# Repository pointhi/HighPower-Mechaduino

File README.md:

View this project on [CADLAB.io](https://cadlab.io/project/1867). 

# HighPower-Mechaduino

KiCad based Mechaduino derivative which drives up to 10A.

This is the original Meachaduino Project: https://hackaday.io/project/11224-mechaduino

**Warning: This Board is currently under development. Simply fabricating it doesn't mean it would work!**
See [v0.1_BUILD_LOG.md](https://github.com/pointhi/HighPower-Mechaduino/blob/master/v0.1_BUILD_LOG.md) for some problems
found while building the first prototype.

A big thanks to the [Shuttleworth Foundation](https://shuttleworthfoundation.org) for supporting the development of this Project.

### Improvements

* ESD protection (especially USB)
* flyback diodes
* stronger drivers
* better silkscreen
* correct use of blocking capacitors
* fuse (for protection against polarity reversal and shorts)
* input voltage measurement
* supply of the microcontroller via the motor voltage supply
* external storage for calibration and configuration data
* Temperature sensor

### Planned Electrical/Mechanical Ratings

* Input Voltage-range of about 12V-50V
* N-Mosfet Driver which is capable of about 10A
* board in the size of NEMA 23 (56x56xmm) or NEMA 24 (60x60mm)

### Interfaces

* USB
* UART (3.3V)
* Step/Dir/Enable (PoStep25-32 Compatible)

### various informations

* [BOM](https://rawgit.com/pointhi/HighPower-Mechaduino/master/pcb/HighPower-Mechaduino.html) can be created using [KiBoM](https://github.com/SchrodingersGat/KiBoM)
* There exists a modified version of the Firmware for this project: [ElektronikNode/Mechaduino-Firmware](https://github.com/ElektronikNode/Mechaduino-Firmware)

## License

Hardware including documentation is licensed under [CERN OHL v.1.2. license](http://www.ohwr.org/licenses/cern-ohl/v1.2)

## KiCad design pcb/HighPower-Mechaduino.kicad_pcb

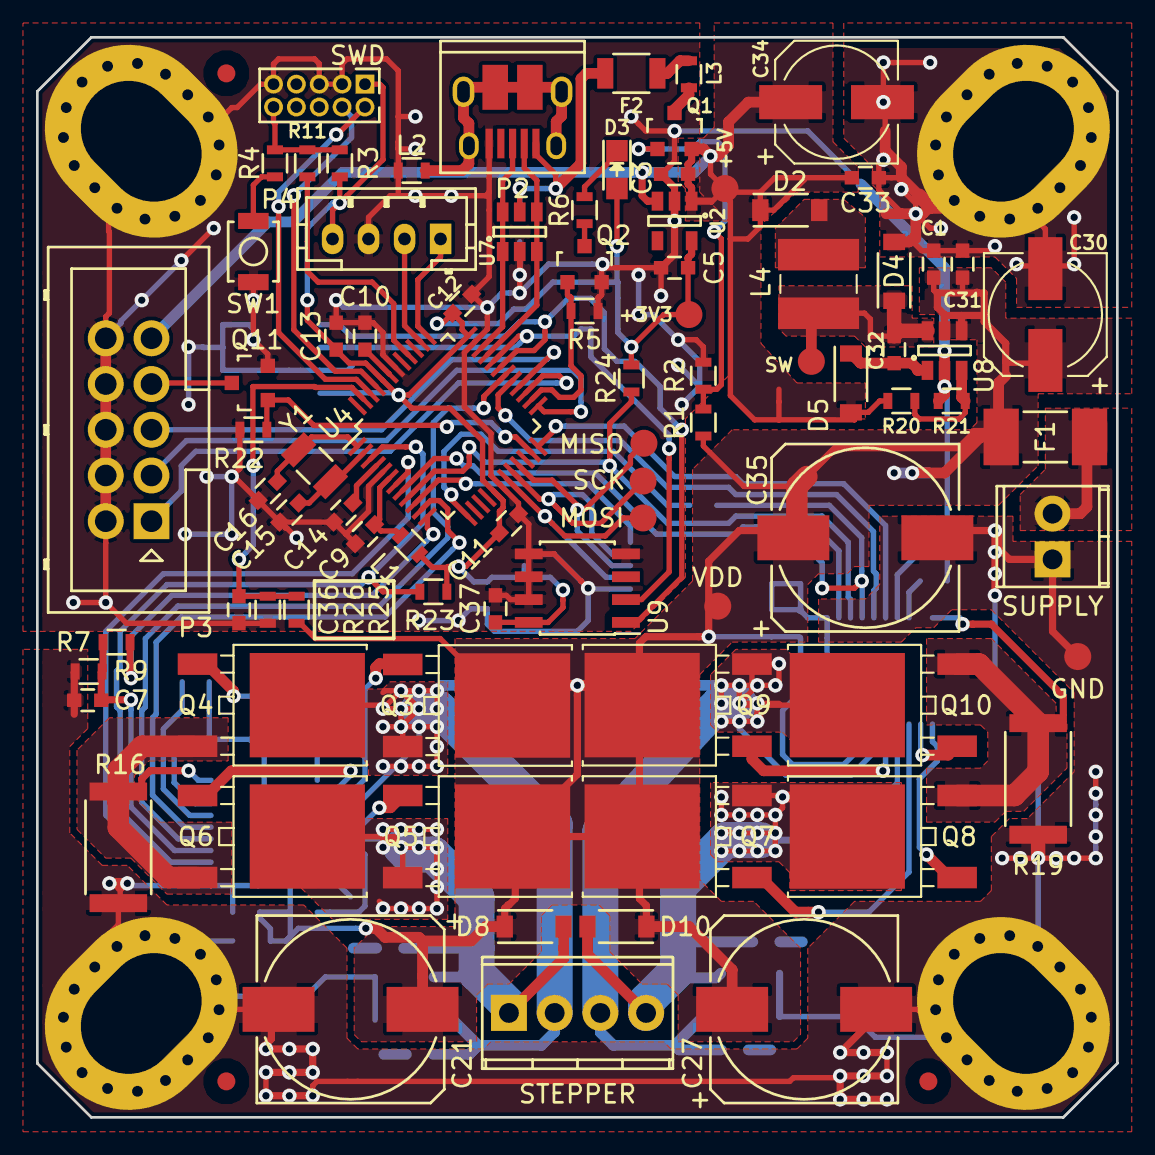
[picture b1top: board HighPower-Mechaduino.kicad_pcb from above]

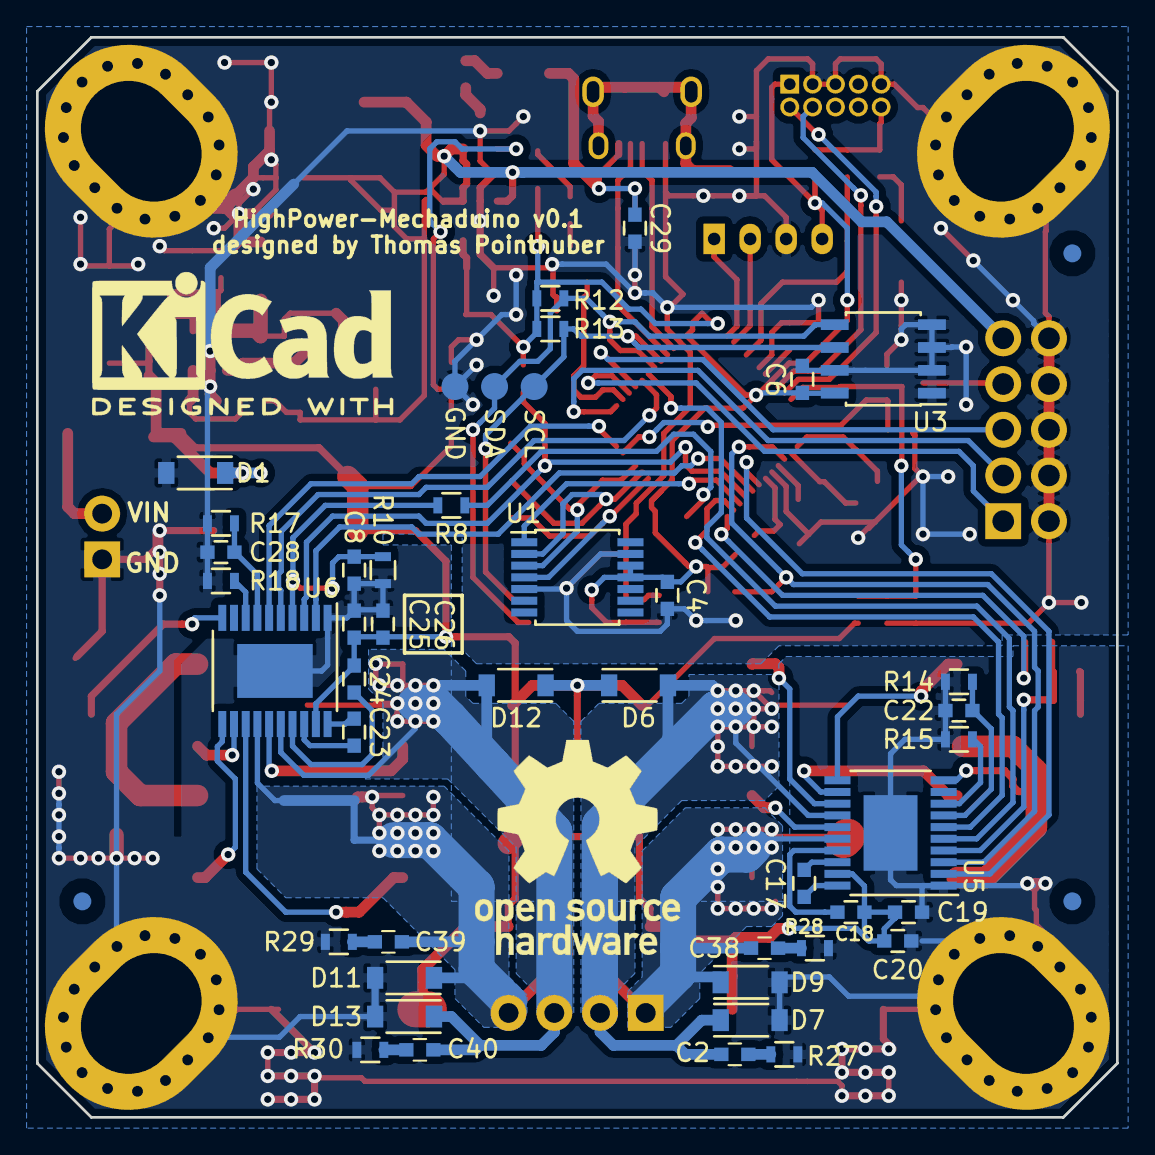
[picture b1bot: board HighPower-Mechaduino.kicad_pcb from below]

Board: 2 copper layers, 60.0 x 60.0 mm, 132 parts (44 on the bottom side), 83 nets.

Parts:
C1, C4, C6, C7, C8, C9, C10, C11, C12, C13, C14, C17, C18, C19, C23, C24, C25, C29, C31, C32, C33, C36, C37: 100n; C_0603
C2, C22, C28, C38, C39, C40: 2.2n; C_0603
C3, C5, C20, C26: 1µ; C_0603
C15, C16: 22p; C_0603
C21, C27, C35: 100µ; c_elec_10x10
C30, C34: 10µ; c_elec_6.6x5.8
D1, D2, D4, D5, D6, D7, D8, D9, D10, D11, D12, D13: RB160M-60; SOD-123
D3: LED; LED_0805
F1: 12A; Fuse_0679H
F2: 500mA; R_1206
J1: SUPPLY; TerminalBlock_Pheonix_MPT-2.54mm_2pol
J2: STEPPER; TerminalBlock_Pheonix_MPT-2.54mm_4pol
L1, L2, L3: MH1608-471Y; R_0603
L4: 22µ; Inductor_Würth_WE-PD2_4532
MK1, MK2, MK3, MK4: Mounting_Hole_PAD; MountingHole_5.3x7.3mm_M5_Pad_Via
P1: SWD; Pin_Header_Straight_2x05_Pitch1.27mm
P2: USB; USB_Micro-B_10103594-0001LF
P3: PoStep25-32; On-Shore-Technology_ED1543_2x05x2.54mm_Straight
P4: CONN_01X04; JST_PH_B4B-PH-K_04x2.00mm_Straight
Q1: SSM3J328R; SOT-23
Q2, Q11: BSS138; SOT-23
Q3, Q4, Q5, Q6, Q7, Q8, Q9, Q10: IPD079N06L3G; PG-TO-252-3-313
R1, R2, R3, R5, R14, R15, R17, R18, R20, R22, R25: 22k; R_0603
R4, R27, R28, R29, R30: 39R; R_0603
R6, R11: 330R; R_0603
R7, R8, R12, R13, R21, R23, R24: 4k7; R_0603
R9, R10, R26: 1k; R_0603
R16, R19: 0R005; R_2512
SW1: B3U-1000P; SW_SPST_B3U-1000P
U1: AS5047D; TSSOP-14_4.4x5mm_Pitch0.65mm
U2: AP2112K-3.3TRG1; SOT-23-5
U3: AT24CS64-SSHM; SOIC-8_3.9x4.9mm_Pitch1.27mm
U4: SAMD21G18A-A; TQFP-48_7x7mm_Pitch0.5mm
U5, U6: A4955GLPTR-T; ETSSOP-20-1EP_4.4x6.5mm_Pitch0.65mm
U7: USBLC6-2SC6; SOT-23-6
U8: MCP16331T; SOT-23-6
U9: LM75BD; SOIC-8_3.9x4.9mm_Pitch1.27mm
W2: VDD; Measurement_Point_Round-SMD-Pad_Small
W3: +5V; Measurement_Point_Round-SMD-Pad_Small
W4, W6: GND; Measurement_Point_Round-SMD-Pad_Small
W5: +3V3; Measurement_Point_Round-SMD-Pad_Small
W11: SDA; Measurement_Point_Round-SMD-Pad_Small
W12: SCL; Measurement_Point_Round-SMD-Pad_Small
W15: MISO; Measurement_Point_Round-SMD-Pad_Small
W16: MOSI; Measurement_Point_Round-SMD-Pad_Small
W17: SCK; Measurement_Point_Round-SMD-Pad_Small
W18: SW; Measurement_Point_Round-SMD-Pad_Small
Y1: G83270022; Crystal_SMD_G8

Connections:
+3V3: C4.2, C5.2, C6.2, C11.2, C12.2, C13.2, C37.2, D3.2, L1.1, P1.1, P4.4, R3.2, R12.1, R13.1, R23.2, R24.2, U1.11, U1.12, U2.5, U3.8, U4.17, U4.36, U4.44, U9.8, W5.1
+5V: C3.2, C33.1, C34.1, D2.1, D5.2, P3.9, Q1.2, R20.2, U2.1, U2.3, W3.1
/AIOUT1: U4.7, U5.2
/AIOUT2: U4.8, U6.2
/A_IN: C36.2, R25.1, R26.2, U4.47
/Arduino_Zero_Base/Arduino_AREF: C14.1, U4.4
/Arduino_Zero_Base/Arduino_RXD: P4.2, U4.38
/Arduino_Zero_Base/Arduino_TXD: P4.1, U4.37
/IN1: U4.11, U5.6
/IN2: U4.30, U5.5
/IN3: U4.24, U6.6
/IN4: U4.29, U6.5
/LED_D13: Q2.1, R5.2, U4.26
/MCP16331_5V/Vfb: R20.1, R21.2, U8.3
/OCLn1: R23.1, U4.3, U5.3
/OCLn2: R24.1, U4.9, U6.3
/PWM_Bridge_A4955-A/OUT1: C38.1, D8.2, D9.1, J2.1, Q5.3, Q6.2, U5.16
/PWM_Bridge_A4955-A/OUT2: C2.1, D6.2, D7.1, J2.2, Q3.3, Q4.2, U5.14
/PWM_Bridge_A4955-A/VREF: C7.2, R7.1, R9.2, U5.4
/PWM_Bridge_A4955-B/OUT1: C40.1, D12.2, D13.1, J2.3, Q9.3, Q10.2, U6.16
/PWM_Bridge_A4955-B/OUT2: C39.1, D10.2, D11.1, J2.4, Q7.3, Q8.2, U6.14
/PWM_Bridge_A4955-B/VREF: C8.2, R8.1, R10.2, U6.4
/Protected_USB_Supply/VBUS: L3.1, Q1.3
/RESET: P1.10, R3.1, R4.2, R11.1
/SCL: R13.2, U3.6, U4.32, U9.2, W12.1
/SDA: R12.2, U3.5, U4.31, U9.1, W11.1
/SPI_CS0: U1.1, U4.10
/SPI_MISO: U1.3, U4.21, W15.1
/SPI_MOSI: U1.4, U4.19, W16.1
/SPI_SCK: U1.2, U4.20, W17.1
/STP_DIR: P3.3, U4.25
/STP_EN: P3.1, U4.27
/STP_ERROR: Q11.1, R22.1, U4.23
/STP_STEP: P3.5, U4.28
/SWCLK: P1.4, U4.45
/SWDIO: P1.2, U4.46
/USB_D+: P2.3, U4.34, U7.1, U7.6
/USB_D-: P2.2, U4.33, U7.3, U7.4
/VREF1: R7.2, U4.12
/VREF2: R8.2, U4.13
GND: C1.1, C3.1, C4.1, C5.1, C6.1, C7.1, C8.1, C9.1, C10.2, C11.1, C12.1, C13.1, C14.2, C15.1, C16.1, C19.2, C20.2, C21.2, C22.2, C25.2, C26.2, C27.2, C28.2, C29.1, C30.2, C31.2, C33.2, C34.2, C35.2, C36.1, C37.1, D1.2, D4.2, D7.2, D9.2, D11.2, D13.2, J1.1, L2.2, MK1.1, MK2.1, MK3.1, MK4.1, P1.3, P1.5, P1.9, P2.5, P3.2, P3.4, P3.6, P3.8, P3.10, P4.3, Q2.2, Q11.2, R2.1, R5.1, R9.1, R10.1, R14.2, R15.2, R16.2, R17.2, R18.2, R19.2, R21.1, R22.2, R26.1, R27.1, R28.1, R29.1, R30.1, SW1.1, U1.5, U1.13, U2.2, U3.1, U3.2, U3.3, U3.4, U3.7, U4.5, U4.18, U4.35, U4.42, U5.1, U5.21, U6.1, U6.21, U7.2, U8.2, U9.4, U9.5, U9.6, U9.7, W4.1, W6.1
unnamed: C2.2, R27.2
unnamed: C9.2, L1.2, U4.6
unnamed: C10.1, U4.43
unnamed: C15.2, U4.2, Y1.1
unnamed: C16.2, U4.1, Y1.2
unnamed: C17.1, U5.20
unnamed: C17.2, U5.18
unnamed: C18.2, U5.17
unnamed: C22.1, R14.1, U5.7
unnamed: C23.1, U6.20
unnamed: C23.2, U6.18
unnamed: C24.2, U6.17
unnamed: C28.1, R17.1, U6.7
unnamed: C29.2, F2.2, P2.1, U7.5
unnamed: C32.1, D5.1, U8.1
unnamed: C32.2, D4.1, L4.1, U8.6, W18.1
unnamed: C38.2, R28.2
unnamed: C39.2, R29.2
unnamed: C40.2, R30.2
unnamed: D2.2, L4.2
unnamed: D3.1, R6.2
unnamed: F1.2, J1.2
unnamed: F2.1, L3.2
unnamed: L2.1, P2.6
unnamed: P3.7, Q11.3
unnamed: Q1.1, R1.1, R2.2
unnamed: Q2.3, R6.1
unnamed: Q3.1, U5.13
unnamed: Q4.1, U5.11
unnamed: Q4.3, Q6.3, R16.1, U5.10
unnamed: Q5.1, U5.15
unnamed: Q6.1, U5.12
unnamed: Q7.1, U6.13
unnamed: Q8.1, U6.11
unnamed: Q9.1, U6.15
unnamed: Q10.1, U6.12
unnamed: Q8.3, Q10.3, R19.1, U6.10
unnamed: R4.1, SW1.2
unnamed: R11.2, U4.40
unnamed: R15.1, U5.8
unnamed: R18.1, U6.8
VDD: C1.2, C18.1, C19.1, C20.1, C21.1, C24.1, C25.1, C26.1, C27.1, C30.1, C31.1, C35.1, D1.1, D6.1, D8.1, D10.1, D12.1, F1.1, Q3.2, Q5.2, Q7.2, Q9.2, R1.2, R25.2, U5.19, U6.19, U8.4, U8.5, W2.1

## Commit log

2016-10-22 Initial version of HighPower-Mechaduino schematic
2016-10-22 Improve README.md
2016-10-22 Fix some assignment problems because of wrong library/component names
2016-10-22 Fix declearation which sizes should be supported
2016-10-22 Place some components onto the PCB
2016-10-23 Export schematic as pdf, close #2
2016-10-24 Place remaining components onto pcb, remove galvanic protection circuit
2016-10-24 First routing try (don't get it as serious design!) Some initial routing so we can check where the design needs improvement
    Problems found:
    * Stepper Drivers should probably be turned, so the driver ic's can be placed on the outside of the pcb
    * rewire arm controller and or place it on the bottom layer
    * think about how to get enough current to the drivers, without disturbing the magnetic sensor
2016-10-28 Improve driver part of PCB I think I improved the Driver part of the PCB quit a bit by rearanging all of the components. But there are still many points which have to be worked on. This is still only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
2016-10-29 Add additional idea
2016-10-29 Improve pcb routing, add testpoints and etc. The design improves a lot. Still lots to do, but most important design parts should now be drafted almost complete.
2016-10-30 This project is now supported by the Shuttleworth Foundation
2016-10-30 Scale image a bit
2016-11-05 Improve pcb
2016-11-05 Improve board routing, add some dukos
2016-11-05 Add oval mounting holes to support NEMA23 as well as NEMA24
2016-11-05 Improve Edge cuts
2016-11-05 Move processor part a bit down
2016-11-05 Add some little changes to the schematic, add calculations
2016-11-15 Add some digikey order informations to components
2016-11-15 Add more order informations, create BOM
2016-11-15 Add link to current BOM
2016-11-15 Add more BOM informations
2016-11-15 Improve BOM
2016-11-17 Use new library symbols
2016-11-19 Improve pcb routing
2016-11-19 Improve layout and add voltage sensing circuit to layout
2016-11-19 Fix inductor (old one was no longer available)
2016-11-19 Add Fiducials to pcb
2016-11-26 Add some improvements, fix issue with schematic error
2016-11-26 Improve pcb (add more part dimensions on the F.Fab layer)
2016-11-26 Fix little schematic error
2016-11-26 update mounting hole symbol
2016-11-26 Add OSHW and KiCad logo
2016-11-29 Improve pcb layout
2016-12-01 Add Digital IO connector
2016-12-01 Fix connector footprint
2016-12-03 Remove connection to SLEEPn Pin
    I think we don't have to connect this pin, and if yes we can fix it manually on the prototype
    The support of Alegro wasn't very helpful about that topic
2016-12-03 Add Text to pcb
2016-12-03 Update Capacitors
2016-12-03 Some little improvements
2016-12-03 Update BOM
2016-12-08 Fix #5
2016-12-08 Fix #7
2016-12-08 Fix schematic error described in #8
2016-12-17 Add initial documentation
2016-12-17 Move documentation
2016-12-17 Improve documentation
2016-12-17 Some more documentation improvements
2016-12-17 Update schematic
2016-12-20 Little update
2017-01-07 Fix #13
2017-01-31 Add FreeCAD model of housing for a NEMA-24 motor (not finished yet)
2017-02-04 Increase hole size to be compatible to M5
2017-02-04 Improve grounding of motor controller (for shunt measurement), Fix #4
2017-02-04 Some little cleanups
2017-02-11 Some changes to the step down converter, Fix #8
2017-02-18 Improve schematic and pcb (add snubber network to driver output)
2017-03-18 Upload initial build log
2017-03-18 Some additions to the Build log
2017-03-25 Add programming manual
2017-03-25 Update buildlog
2017-03-25 Other doc header
2017-04-01 Some testcodes
2017-10-21 Improve README and update buildlog
2017-10-21 Reposition text
2019-06-13 Backlink to CADLAB.io has been added.
